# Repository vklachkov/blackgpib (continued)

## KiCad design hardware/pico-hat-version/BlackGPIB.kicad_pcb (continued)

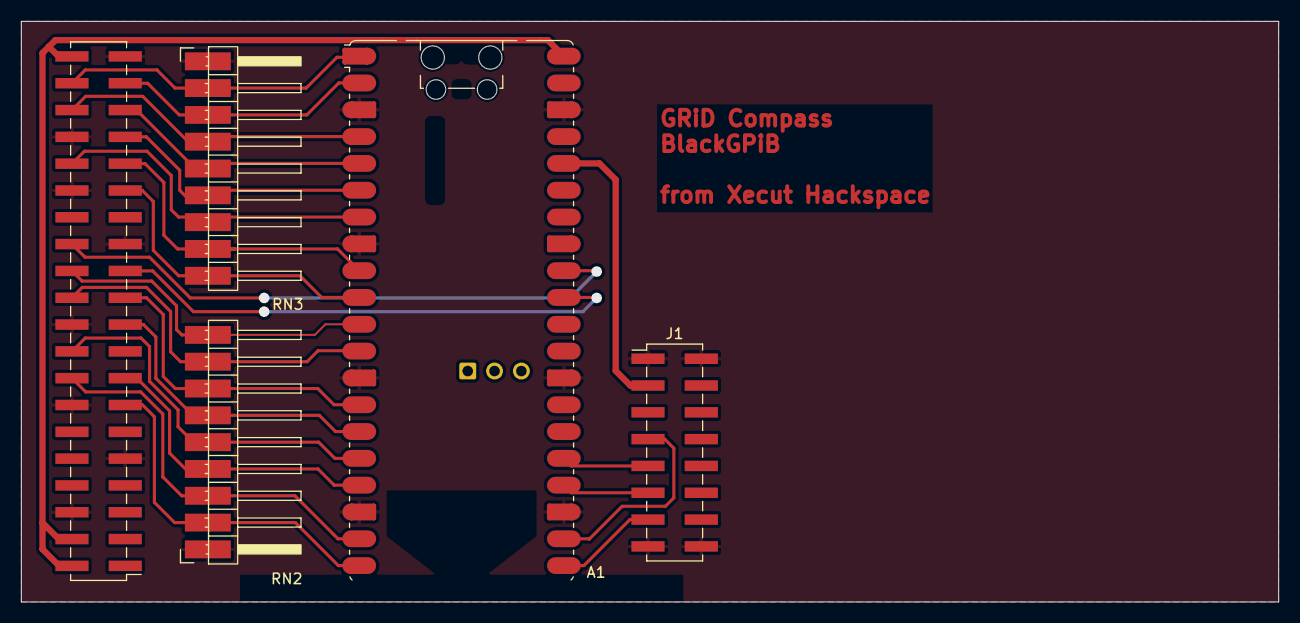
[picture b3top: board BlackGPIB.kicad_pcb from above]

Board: 2 copper layers, 119.1 x 55.0 mm, 5 parts (0 on the bottom side), 25 nets.

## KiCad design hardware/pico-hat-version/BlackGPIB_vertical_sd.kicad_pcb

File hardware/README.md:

# First board by @JDat for Raspberry Pi 2+

This is the first revision of the board, designed by @JDat (also known as @YL3AKC):

> [!WARNING]
> It is better to wait for the second revision or new Pico base version. This board is still experimental.

## Components

| Part           | Value                | Package    | Quantity |
|----------------|----------------------|------------|----------|
| GPIB Connector | -                    | 90 Degree  | 1        |
| SN75160B       | -                    | SMD or DIP | 1        |
| SN75161B       | -                    | SMD or DIP | 1        |
| Resistor       | 2kΩ                  | 0805       | 20       |
| Capacitor      | 0.1uF                | 0805       | 2        |
| Pin Header     | 20x2 Straight Female | -          | 1        |

P.S. Instead of small SMD components, you can also use through-hole components, as Kirill @BOOtak Leyfer did.

https://t.me/bootaks_old_devices/286

## Errata

### ATN <-> SRQ

ATN and SRQ are mixed up on the board. Both the labels and the pins on the connector are swapped.

For the board to work correctly, you need to cut two tracks on the back side that go to SRQ and ATN, and solder two jumpers, as shown in the photo:

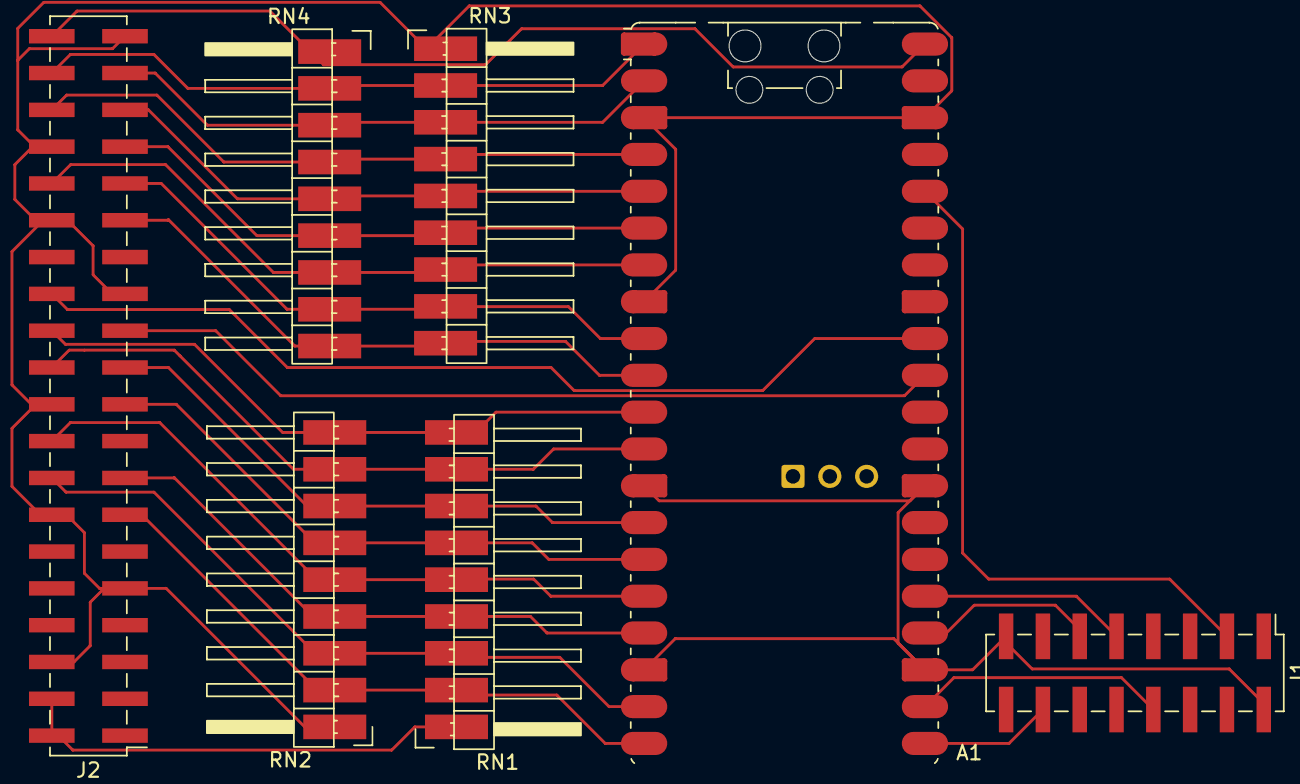
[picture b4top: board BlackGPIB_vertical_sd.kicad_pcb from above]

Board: 2 copper layers, 7 parts (0 on the bottom side), 25 nets.

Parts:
A1: RaspberryPi_Pico; RaspberryPi_Pico_W_SMD_HandSolder
J1: SD_Card_Module; PinHeader_2x08_P2.54mm_Vertical_SMD
J2: Raspberry_Pi_Connector; PinHeader_2x20_P2.54mm_Vertical_SMD
RN1, RN4: 3K3; PinHeader_1x09_P2.54mm_Horizontal_Left
RN2, RN3: 6K8; PinHeader_1x09_P2.54mm_Horizontal_Right

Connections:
+3.3V: A1.36 (3V3), J1.3 (3.3V), J1.4 (3.3V)
+5V: A1.40 (VBUS), J2.2 (5V), J2.4 (5V), J2.40 (PE), RN1.1 (common), RN4.1 (common)
GND: A1.3 (GND), A1.8 (GND), A1.13 (GND), A1.18 (GND), A1.23 (GND), A1.28 (GND), A1.38 (GND), J1.1 (GND), J1.2 (GND), J1.15 (GND), J1.16 (GND), J2.6 (GND), J2.9 (GND), J2.14 (GND), J2.20 (GND), J2.25 (GND), J2.30 (GND), J2.34 (GND), J2.39 (GND), RN2.1 (common), RN3.1 (common)
GPIB_ATN: A1.14 (GPIO10), J2.21 (ATN), RN1.7 (R6), RN2.7 (R6)
GPIB_DAV: A1.15 (GPIO11), J2.19 (DAV), RN1.6 (R5), RN2.6 (R5)
GPIB_DC: A1.31 (GPIO26_ADC0), J2.23 (DC)
GPIB_DIO1: A1.10 (GPIO7), J2.29 (DIO1), RN3.9 (R8), RN4.9 (R8)
GPIB_DIO2: A1.9 (GPIO6), J2.31 (DIO2), RN3.8 (R7), RN4.8 (R7)
GPIB_DIO3: A1.7 (GPIO5), J2.32 (DIO3), RN3.7 (R6), RN4.7 (R6)
GPIB_DIO4: A1.6 (GPIO4), J2.33 (DIO4), RN3.6 (R5), RN4.6 (R5)
GPIB_DIO5: A1.5 (GPIO3), J2.35 (DIO5), RN3.5 (R4), RN4.5 (R4)
GPIB_DIO6: A1.4 (GPIO2), J2.36 (DIO6), RN3.4 (R3), RN4.4 (R3)
GPIB_DIO7: A1.2 (GPIO1), J2.37 (DIO7), RN3.3 (R2), RN4.3 (R2)
GPIB_DIO8: A1.1 (GPIO0), J2.38 (DIO8), RN3.2 (R1), RN4.2 (R1)
GPIB_EOI: A1.12 (GPIO9), J2.22 (EOI), RN1.8 (R7), RN2.8 (R7)
GPIB_IFC: A1.19 (GPIO14), J2.16 (IFC), RN1.3 (R2), RN2.3 (R2)
GPIB_NDAC: A1.17 (GPIO13), J2.15 (NDAC), RN1.4 (R3), RN2.4 (R3)
GPIB_NRFD: A1.16 (GPIO12), J2.18 (NRFD), RN1.5 (R4), RN2.5 (R4)
GPIB_REN: A1.20 (GPIO15), J2.13 (REN), RN1.2 (R1), RN2.2 (R1)
GPIB_SRQ: A1.11 (GPIO8), J2.24 (SRQ), RN1.9 (R8), RN2.9 (R8)
GPIB_TE: A1.32 (GPIO27_ADC1), J2.26 (TE)
SPI_CS: A1.22 (GPIO17), J1.7 (CS), J1.8 (CS)
SPI_MISO: A1.21 (GPIO16), J1.13 (MISO), J1.14 (MISO)
SPI_MOSI: A1.25 (GPIO19), J1.9 (MOSI), J1.10 (MOSI)
SPI_SCK: A1.24 (GPIO18), J1.11 (SCK), J1.12 (SCK)

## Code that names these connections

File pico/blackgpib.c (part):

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////////////////////////////////////////////////////////////////////////////////

void init_gpio_pins(void) {
  gpio_set_function(PIN_GPIB_TE, GPIO_FUNC_SIO);
  gpio_set_dir(PIN_GPIB_TE, GPIO_OUT);

  gpio_set_function(PIN_GPIB_DC, GPIO_FUNC_SIO);
  gpio_set_dir(PIN_GPIB_DC, GPIO_OUT);
}

__attribute__((always_inline))
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////////////////////////////////////////////////////////////////////////////////

void gpib_configure_listener(void) {  
  configure_input(PIN_GPIB_ATN);
  configure_output(PIN_GPIB_SRQ);
  configure_input(PIN_GPIB_REN);
  configure_input(PIN_GPIB_IFC);
  configure_input(PIN_GPIB_EOI);
  configure_input(PIN_GPIB_DAV);

  configure_output(PIN_GPIB_NDAC);
  configure_output(PIN_GPIB_NRFD);

  configure_input(PIN_GPIB_DIO1);
  configure_input(PIN_GPIB_DIO2);
  configure_input(PIN_GPIB_DIO3);
  configure_input(PIN_GPIB_DIO4);
  configure_input(PIN_GPIB_DIO5);
  configure_input(PIN_GPIB_DIO6);
  configure_input(PIN_GPIB_DIO7);
  configure_input(PIN_GPIB_DIO8);

  gpio_put(PIN_GPIB_DC, true);
  gpio_put(PIN_GPIB_TE, false);
}

uint8_t gpib_read_byte(void) {
  uint8_t result = 0;
  result |= (uint8_t)(!gpio_get(PIN_GPIB_DIO1)) << 0;
  result |= (uint8_t)(!gpio_get(PIN_GPIB_DIO2)) << 1;
  result |= (uint8_t)(!gpio_get(PIN_GPIB_DIO3)) << 2;
  result |= (uint8_t)(!gpio_get(PIN_GPIB_DIO4)) << 3;
  result |= (uint8_t)(!gpio_get(PIN_GPIB_DIO5)) << 4;
  result |= (uint8_t)(!gpio_get(PIN_GPIB_DIO6)) << 5;
  result |= (uint8_t)(!gpio_get(PIN_GPIB_DIO7)) << 6;
  result |= (uint8_t)(!gpio_get(PIN_GPIB_DIO8)) << 7;
  return result;
}

gpib_cmd_t gpib_start_command_handshake(void) {
  while (true) {
    if (gpio_get(PIN_GPIB_ATN)) {
      gpio_put(PIN_GPIB_NDAC, true);
      continue;
    }

    gpio_put(PIN_GPIB_NDAC, false);

    if (gpio_get(PIN_GPIB_DAV)) {
      continue;
    }

    gpio_put(PIN_GPIB_NRFD, false);

    uint8_t byte = gpib_read_byte();
    return gpib_parse_cmd(byte);
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}

void gpib_unexpected_byte(void) {
  gpio_put(PIN_GPIB_NDAC, true);

  while (!gpio_get(PIN_GPIB_DAV)) {}

  gpio_put(PIN_GPIB_NRFD, true);
}

void gpib_end_handshake(void) {
  gpio_put(PIN_GPIB_NRFD, false);
  gpio_put(PIN_GPIB_NDAC, true);

  while (!gpio_get(PIN_GPIB_DAV)) {}

  gpio_put(PIN_GPIB_NDAC, false);
  gpio_put(PIN_GPIB_NRFD, true);
}

typedef struct {
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} gpib_byte_t;

gpib_byte_t gpib_start_data_handshake(void) {
  gpio_put(PIN_GPIB_NDAC, false);

  while (gpio_get(PIN_GPIB_DAV)) {}

  uint8_t value = gpib_read_byte();
  bool atn = gpio_get(PIN_GPIB_ATN);
  bool eoi = gpio_get(PIN_GPIB_EOI);

  return (gpib_byte_t){ value, atn, eoi };
}
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////////////////////////////////////////////////////////////////////////////////

void gpib_configure_talker(void) {
  configure_output(PIN_GPIB_ATN);
  configure_input(PIN_GPIB_SRQ);
  configure_output(PIN_GPIB_REN);
  configure_output(PIN_GPIB_IFC);
  configure_output(PIN_GPIB_EOI);
  configure_output(PIN_GPIB_DAV);

  configure_input(PIN_GPIB_NDAC);
  configure_input(PIN_GPIB_NRFD);

  configure_output(PIN_GPIB_DIO1);
  configure_output(PIN_GPIB_DIO2);
  configure_output(PIN_GPIB_DIO3);
  configure_output(PIN_GPIB_DIO4);
  configure_output(PIN_GPIB_DIO5);
  configure_output(PIN_GPIB_DIO6);
  configure_output(PIN_GPIB_DIO7);
  configure_output(PIN_GPIB_DIO8);

  gpio_put(PIN_GPIB_DC, false);
  gpio_put(PIN_GPIB_TE, true);
}

void gpib_write_byte(uint8_t byte) {
  const uint8_t pins[8] = { PIN_GPIB_DIO1, PIN_GPIB_DIO2, PIN_GPIB_DIO3, PIN_GPIB_DIO4, PIN_GPIB_DIO5, PIN_GPIB_DIO6, PIN_GPIB_DIO7, PIN_GPIB_DIO8 };

  for (size_t i = 0; i < 8; i++) {
    gpio_put(pins[i], !(byte >> i & 0b1));
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}

void gpib_send_byte(uint8_t byte, bool eoi) {
  gpio_put(PIN_GPIB_EOI, !eoi);
  gpib_write_byte(byte);

  sleep_us(10);

  while (gpio_get(PIN_GPIB_NDAC) || !gpio_get(PIN_GPIB_NRFD)) {}

  // Now we can signal that data is valid.
  gpio_put(PIN_GPIB_DAV, false);

  // Wait until the laptop signals successful data read.
  while (!gpio_get(PIN_GPIB_NDAC)) {}

  // Signal that data is no longer valid.
  gpio_put(PIN_GPIB_DAV, true);

  gpio_put(PIN_GPIB_EOI, true);
}

void gpib_send_serial_poll_response(uint8_t byte) {
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}

void gpib_send_bytes(const uint8_t *data, size_t size) {
  gpio_put(PIN_GPIB_ATN, true);

  for (size_t i = 0; i < size; i++) {
    gpib_send_byte(data[i], i == size - 1);
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  disk_resp_t resp = (disk_resp_t) { DISK_RESP_OK };
  emu->buffer_len = disk_resp_serialize(&resp, (uint8_t*)&emu->buffer, SECTOR_SIZE);

  gpio_put(PIN_GPIB_SRQ, false);

  return;
}
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          bool srq_required = disk_emu_process_buffer(&emu->disk_emu,
                                                      emu->buffer, emu->buffer_len);
          if (srq_required) {
            gpio_put(PIN_GPIB_SRQ, false);
            emu->srq_raised = true;
          }

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
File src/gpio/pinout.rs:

//! Valid pin list for the BlackGPiB board.

#[derive(Clone, Copy, Debug)]
#[repr(u8)]
pub enum KnownPin {
    /// Transfer Enable/Talk Enable (SN75161 and 162).
    TE = 7,
    /// Direction Control (SN75161 and 162).
    DC = 11,
    /// System Control (SN75162 only).
    SC = 17,
    /// System Control (SN75161 and 162).
    PE = 21,

    /// Data Input/Output, bit 1.
    DIO1 = 5,
    /// Data Input/Output, bit 2.
    DIO2 = 6,
    /// Data Input/Output, bit 3.
    DIO3 = 12,
    /// Data Input/Output, bit 4.
    DIO4 = 13,
    /// Data Input/Output, bit 5.
    DIO5 = 19,
    /// Data Input/Output, bit 6.
    DIO6 = 16,
    /// Data Input/Output, bit 7.
    DIO7 = 26,
    /// Data Input/Output, bit 8.
    DIO8 = 20,

    /// Data Available.
    DAV = 10,
    /// Not Ready For Data.
    NRFD = 24,
    /// Not Data Accepted.
    NDAC = 22,

    /// Attention.
    ATN = 9,
    /// Interface Clear.
    IFC = 23,
    /// Service Request.
    SRQ = 8,
    /// Remote Enable.
    REN = 27,
    /// End Or Identify.
    EOI = 25,
}

impl KnownPin {
    pub const fn all() -> [Self; 20] {
        [
            KnownPin::TE,
            KnownPin::DC,
            KnownPin::SC,
            KnownPin::PE,
            KnownPin::DIO1,
            KnownPin::DIO2,
            KnownPin::DIO3,
            KnownPin::DIO4,
            KnownPin::DIO5,
            KnownPin::DIO6,
            KnownPin::DIO7,
            KnownPin::DIO8,
            KnownPin::DAV,
            KnownPin::NRFD,
            KnownPin::NDAC,
            KnownPin::ATN,
            KnownPin::IFC,
            KnownPin::SRQ,
            KnownPin::REN,
            KnownPin::EOI,
        ]
    }

    pub const fn data() -> [KnownPin; 8] {
        [
            KnownPin::DIO1,
            KnownPin::DIO2,
            KnownPin::DIO3,
            KnownPin::DIO4,
            KnownPin::DIO5,
            KnownPin::DIO6,
            KnownPin::DIO7,
            KnownPin::DIO8,
        ]
    }
}

const _: () = {
    let pins = KnownPin::all();

    let mut i = 0;
    while i < pins.len() {
        assert!((pins[i] as u8) < 32, "all pins must be in range 0..32");
        i += 1;
    }
};

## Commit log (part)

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2025-10-28 Kirill Leyfer's unfinished emulator
2025-10-29 add devcontainer to develop this project on Macbook
2025-10-29 try to adapt sources to the new board
2025-10-29 add rust to devcontainer for next version
2025-10-31 add docs for gpib controller and gpib standard
2025-10-31 newver: listen bytes on gpib bus
2025-10-31 newver: enable pullups in sn75161/162
2025-10-31 newver: fix byte read
2025-10-31 change project structure
2025-10-31 newver: move listener state machine to file, remove LADS state
2025-11-01 setup all data pins before read
2025-11-01 speedup data reading, fix last byte loss
    Compass reset data lines without waiting for the disk, without waiting for us to raise the NDAC. This is a violation of the standard, but there's nothing we can do about it. We just need to read the 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
    It's a dangerous situation, but there's no solution yet.
2025-11-01 unwrap all gpio errors, remove all ???????
2025-11-01 add first logs from new implementation
2025-11-01 add gpib pinout to docs
2025-11-01 newver: implement listener state machine
2025-11-01 move reader logic to Listener struct
2025-11-01 parse requests
2025-11-02 add more comments to Listener
2025-11-02 talker stub
2025-11-02 shitty talker
2025-11-03 describe all known and supported dev addresses as enum
2025-11-03 use log crate and hand made logger instead of println's
2025-11-03 add parser for gpib commands and remove all is_smth functions
2025-11-03 add ieee 488.2
2025-11-03 add more pain
2025-11-04 create disk info struct
    no more big, ugly and weird byte arrays
2025-11-04 remove unused commands from GPIBCommand, add tests
2025-11-04 add docs and basic tests for Request
2025-11-04 code refactoring and documentation
2025-11-04 add Makefile for build and deploy
2025-11-04 try to refactor listener
2025-11-05 move next command wait logic to main
2025-11-05 fix makefile
2025-11-06 first working version
2025-11-07 pass image as console argument
2025-11-07 try to docs DiskIdentity structure
2025-11-07 patch image in-memory on write request
2025-11-07 try to debug boot from emu
2025-11-07 first boot from emulator
2025-11-09 serialize GPIBCommand and write round trip tests
2025-11-09 add utils to Talker for future master variant
2025-11-09 break everything, prepare for rewriting
2025-11-09 remove thiserror dependency
2025-11-09 doc every field in DiskIdentity
2025-11-09 custom rt logger from Cursor
2025-11-10 revert "custom rt logger from Cursor"
    this reverts commit 42d3d88642f886ec6d2344506e6bbc0f9c20d821.
2025-11-10 write new very safe logger with ringbuf crate
2025-11-10 configure scheduler: set core affinity and process priority
2025-11-10 prototype of device manager
2025-11-10 implement disk emulator based on new api
2025-11-10 fix serial poll tracking, first boot with new disk emu
2025-11-11 implement in memory write for disk emulator
2025-11-11 refactor code, prepare for open source
2025-11-11 feeble attempt to tidy up repo
2025-11-11 experiments with plotter
2025-11-11 create common device that proxy listened data to unix socket
2025-11-12 broadcast to udp port instead of unix socket
2025-11-12 add experimental hack to wait next command after GPiB state breakage
2025-11-12 add JDat's board
2025-11-12 add first README
2025-11-12 configure log level
2025-11-12 remove images hardcode, use cli args
2025-11-12 add flag to enable trace or verbose logs
2025-11-12 clear buffer after request processing, fix crash on Write
2025-11-12 pass message by ref to logger
2025-11-12 temporary hack for issue #6, fix MS-DOS 2.11 boot
2025-11-12 hack Initialize request for issue #2, fix MS-DOS 2.00A boot
2025-12-01 pin blackgpib to core 3, without available parallelism math
2025-12-01 enable pullups, fix bus hang when second device connected
2025-12-01 mmap images, allow to write data to disk
2025-12-01 log byte on atn break
2025-12-06 implement Format request
2025-12-07 implement sniffer
    I'm too tired of the logic analyzer
2025-12-07 fix Format, initialize only first 8 bytes with 0xFF
2025-12-07 add response structure for disk emulator and fix response for Write req
2025-12-08 fix new dump parsing in gpib-dump-analyzer
2025-12-08 configure scheduller before running sniffer
2025-12-08 rework all logs in gpib-dump-analyzer
    display parsed and raw requests and responses, display serial poll bytes in full mode and refactor state handling
2025-12-08 rename analyzer to dump_parser
2025-12-08 parse disk status responses in gpib-dump-parser
2025-12-08 fix typo in DiskStatus
2025-12-09 rename folder devices to emulator
2025-12-09 change cli interface of dump analyzer
    use bpaf, return --compact instead of only_requests|full
2025-12-09 set SRQ after UNL, not after last byte
2025-12-09 connect only requested disks
    Previously, to debug the emulator with a real device on bus, it was necessary to comment some addresses in KnownDevices.
    Also emulator incorrectly handled "uninserted" image, which cause issues with laptop.
    There is no measurable difference in speed between the old approach and the new one, but this makes further improvements much easier.
2025-12-09 refactor new requests parser in disk emulator
2025-12-09 detect unformatted disks
2025-12-09 fix "Broken pipe" panic in gpib-dump-parser
2025-12-09 stub for controller emulator
2025-12-09 add some dumps from sniffer
2025-12-10 move emulator/manager to emulator/mod
2025-12-10 handle unsupported requests like real disk
2025-12-15 rewrite listener gpib handshake from scratch
    After reverse engineering the 2101 floppy drive firmware, it turned out
    that the floppy drive behaves differently on the bus.
    I decided not to follow the standard, but to transfer the logic from the
    original peripheral.
    This doesn’t fix anything explicitly, but now I’m confident in the
    correctness of the handshakes and command handling.
2025-12-16 slightly fix talker
2025-12-16 do not reset ndac if dav is high on command handshake
2025-12-16 fix serial poll state machine
2025-12-21 hack nanosleep with busy_wait
    fixes awful 2ms lag on gpio configuration
2025-12-21 wait atn inside talker
2025-12-22 fork rppal, remove all thread safe code and std::thread::sleep
2025-12-22 rewrite busy_wait using cntfrq и cntvct
2025-12-22 rename rppal to gpio, prepare for rewriting gpio part of project
2025-12-23 first step of gpio rewriting: break everything, reimplement listener
2025-12-23 reimplement talker using new gpio module
2025-12-23 implement read_dio in listener gpio
2025-12-23 configure all pins in listener and talker
2025-12-24 rework talker to dc=low, te=high and remove bias setup
2025-12-25 move system outside of gpio, open gpio in main
2025-12-25 remove all unused features from gpio, make it less unsafe
2025-12-25 move all gpib related code to gpib folder and reorganize utils
2025-12-25 rework error handling in main
2025-12-25 fix logs, add comments
2025-12-25 add doc comments for files from rppal
2025-12-26 disable priority configuration
2025-12-26 make talker logs less verbose
2025-12-26 configure gpio pins before touching SN7516x control pins
2025-12-26 restore sniffer
2025-12-26 fix structure of disk's StatusResponse
2025-12-26 rename drive_ready to drive_status and improve tests in disk emulator
2025-12-26 write diskette using blackgpib
2025-12-26 add OutOfBoundsWrite to DiskStatus
2025-12-26 add cli commands to read, write and format gpib disks
2025-12-26 implement reset and format in DeviceController
2025-12-26 fix code after bad rebase
2025-12-27 rework logs for controller mode, improve error handling
2025-12-27 fix talker and listener for controller mode (emulator still works)
2025-12-27 wait 15 seconds after reset like real laptop
2025-12-27 add "controller status" command to get info about gpib device
2025-12-28 move disk protocol files to crate level
2025-12-28 remove asserts in controller, replace with proper error handling
2025-12-28 rewrite logs and error in controller format command
2025-12-28 add more logs to controller mode
2025-12-28 prevent blackgpib from running on Raspberry Pi 1
    because blackgpib requires one dedicated core
2025-12-28 add delays to Talker::send_command
2025-12-28 remove all panics from emulator
2025-12-28 fix all TODOs in controller mode help
2025-12-29 Refactor disk protocol
2025-12-29 check mode instead of sector when handling Write(0xFFFFFFFF) request
2026-01-13 update disk protocol after reverse engineering 2101
2026-02-01 add pico hatted board schematic
2026-02-01 add pico hello world
2026-02-01 fix pico hatted version: swap dc te and fix dc te on schematic
2026-02-02 move board from @JDat to separate folder
2026-02-02 move linux version source code to subdirectory "pi"
2026-02-03 pi pico demo firmware (just to test hardware)
2026-02-07 fix voltage divider for pico hat hardware
2026-02-07 fix gpib address in pico firmware
2026-02-07 continue debugging pico version
2026-02-08 pico: fix handshakes in listening function
2026-02-08 pico: fix logs, continue debugging
2026-02-08 pico: invert bits when sending byte
2026-02-08 pico: fix request handling
2026-02-08 pico: split request handling to multiple functions
2026-02-08 pico: fix srq handling, first boot without any timeout issues
2026-02-08 pico: read/write data from/to sd card
2026-02-09 pico: split firmware into multiple files
2026-02-10 optimize gpib pins configuration
2026-02-11 pico: optimize hatted version for SLA printer, remove optional components
2026-02-14 pico: add ground polygon and improve traces in hatted version
2026-02-15 pico: move DC TE traces in hatted version to make handicraft easier
2026-02-15 pico: fix several warnings and UBs
2026-02-18 pi: swap srq and atn on the gpib hat and fix import issues
2026-02-19 pi: update README.md for hardware
2026-02-23 pico: add rev 1 board
2026-02-23 pico: add 47uF tantalum capacitor near sd card slot to rev 1 board
2026-02-23 pico: fix disconnected pads and zones on rev 1 board
2026-05-09 pico: fix pinout for rev 1 board, configure PE
2026-06-01 rewrite readme for all folders, add license and remove old pdf files
2026-06-01 fix main readme license section header
2026-06-01 pico: move all file operations to loaders, handle sd card errors
2026-06-01 pico: blink on gpib activity
2026-06-01 pico: replace all printfs with LOG_* macro, disable debug logs
2026-06-01 pico: support multiple devices, but still use demo images
2026-06-02 pico: guess geometry in img loader
2026-06-02 pico: select disk parameters based on image geometry
2026-06-02 pico: support image formatting
2026-06-02 pico: code format, fix compilation
2026-06-02 pico: fix handshake for MLA gpib command
2026-06-04 pico: load list of images from sd card, move sd card ops to sd_card.c
2026-06-04 pico: refactor logging, save some logs to sd card
2026-06-04 pico: reboot loop protection to save sd card
2026-06-04 pico: do not remount fs in sd_card_get_image_loaders, fix boot
2026-06-04 pico: add more logs for errors
2026-06-04 pico: sync files after write
2026-06-04 pico: add manual to README.md
